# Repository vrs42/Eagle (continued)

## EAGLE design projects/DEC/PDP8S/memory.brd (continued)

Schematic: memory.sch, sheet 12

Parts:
A03: R001S; H807S
A04: R202S; H807S
A09: R107S; H807S
A11, A34: R111S; H807S
A12: R002S; H807S
A16: R602U; H807S
A19: R603S; H807S
B02: W023S; H807S
B03: W050S; H807S
B04: R202S; H807S
B05: W005S; H807S
B18: R603S; H807S
B24: R113S; H807S
B33: R107S; H807S
B39: W028S; H807S
C02: W023S; H807S
C04: R202S; H807S
C05: R107S; H807S
D02: W023S; H807S
D03: W050S; H807S
D04: R202S; H807S
D05: R107S; H807S
D06: R113S; H807S
E02: W023S; H807S
E03: R001S; H807S
E04: R202S; H807S
E08: W005S; H807S
E37, E38, E39: W028S; H807S
F03, F04: R202S; H807S
F06: R001S; H807S
F08, F09: R111S; H807S
F10: R107S; H807S
F14: R113S; H807S

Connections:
-15V: A03.B2 (-15V), A04.B2 (-15V), A09.B2 (-15V), A11.B2 (-15V), A12.B2 (-15V), A16.B2 (-15V), A19.B2 (-15V), A34.B2 (-15V), B03.B2 (-15V), B04.B2 (-15V), B05.B2 (-15V), B18.B2 (-15V), B24.B2 (-15V), B33.B2 (-15V), C04.B2 (-15V), C05.B2 (-15V), D03.B2 (-15V), D04.B2 (-15V), D05.B2 (-15V), D06.B2 (-15V), E03.B2 (-15V), E04.B2 (-15V), E08.B2 (-15V), F03.B2 (-15V), F04.B2 (-15V), F06.B2 (-15V), F08.B2 (-15V), F09.B2 (-15V), F10.B2 (-15V), F14.B2 (-15V); also elsewhere on the board
-(DP+EP): A19.P2; also elsewhere on the board
-(SP+PCP): A19.J2; also elsewhere on the board
-(WTX*ROTR): A16.F2 (F); also elsewhere on the board
-(WTX*TAD): A16.J2 (J); also elsewhere on the board
-A12: A16.H2 (H), A19.D2 (PU0); also elsewhere on the board
-A(00-01): A16.E2 (E); also elsewhere on the board
-A(00-11): B18.K2 (PU0); also elsewhere on the board
-AC11: A03.E2 (E), A04.T2 (1), A09.S2; also elsewhere on the board
-BAC00: D05.F2, E39.D2
-BAC01: D05.J2, E39.E2
-BAC02: D05.L2, E39.H2
-BAC03: D05.N2, E39.K2
-BAC04: D05.R2, E39.M2
-BAC05: D05.T2, E39.P2
-BAC06: C05.F2, E39.S2
-BAC07: C05.J2, E39.T2
-BAC08: C05.L2, E39.V2
-BAC09: B39.D2, C05.N2
-BAC10: B39.E2, C05.R2
-BAC11: B39.H2, C05.D2
-CAC: A04.M2 (SET), A19.F2 (O), A19.M2 (O), B04.M2 (SET), C04.M2 (SET), D04.M2 (SET), E04.M2 (SET), F04.M2 (SET); also elsewhere on the board
-CL: F03.F2 (RESET); also elsewhere on the board
-IC00: B05.V2, E03.D2 (D), E38.D2
-IC01: B05.U2, E03.F2 (D), E38.E2
-IC02: B05.T2, E03.J2 (D), E38.H2
-IC03: B05.S2, E03.L2 (D), E38.K2
-IC04: B05.R2, E03.N2 (D), E38.M2
-IC05: A03.T2 (D), B05.P2, E38.P2
-IC06: A03.R2 (D), B05.N2, E38.S2
-IC07: A03.N2 (D), B05.M2, E38.T2
-IC08: A03.L2 (D), B05.L2, E38.V2
-IC09: A03.J2 (D), B05.K2, E37.D2
-IC10: A03.F2 (D), B05.J2, E37.E2
-IC11: A03.D2 (D), B05.H2, E37.H2
-L: F03.H2 (0), F06.E2 (E); also elsewhere on the board
-LP: A19.K2 (PU0); also elsewhere on the board
-LSH: F03.D2 (PU0), F03.K2 (PU1); also elsewhere on the board
-SAC00: E08.U2, F04.F2 (RESET); also elsewhere on the board
-SAC01: E08.T2, F04.R2 (RESET); also elsewhere on the board
-SAC02: E04.F2 (RESET), E08.S2; also elsewhere on the board
-SAC03: E04.R2 (RESET), E08.R2; also elsewhere on the board
-SAC04: D04.F2 (RESET), E08.P2; also elsewhere on the board
-SAC05: D04.R2 (RESET), E08.N2; also elsewhere on the board
-SAC06: C04.F2 (RESET), E08.M2; also elsewhere on the board
-SAC07: C04.R2 (RESET), E08.H2; also elsewhere on the board
-SAC08: B04.F2 (RESET), E08.K2; also elsewhere on the board
-SAC09: B04.R2 (RESET), E08.F2; also elsewhere on the board
-SAC10: A04.F2 (RESET), E08.E2; also elsewhere on the board
-SAC11: A04.R2 (RESET), E08.D2; also elsewhere on the board
-SL: F06.D2 (D); also elsewhere on the board
-TAD: F06.J2 (D); also elsewhere on the board
AC00: D03.P2, D05.H2, F04.H2 (0), F04.V2 (EN1); also elsewhere on the board
AC11B: A09.R2, A34.S2, B03.E2, F08.D2, F09.K2; also elsewhere on the board
AND: F06.T2 (D); also elsewhere on the board
AND+TAD+DCA+IAC+CMA+ROTL+OP2: B24.M2; also elsewhere on the board
DC: A34.R2; also elsewhere on the board
EX+DC: B33.H2; also elsewhere on the board
GND: A03.C2 (GND), A04.C2 (GND), A09.C2 (GND), A11.C2 (GND), A12.C2 (GND), A16.C2 (GND), A19.C2 (GND), A19.H2 (G), A19.L2 (EN0), A19.N2 (G), A34.C2 (GND), B03.C2 (GND), B04.C2 (GND), B05.C2 (GND), B18.C2 (GND), B18.N2 (G), B24.C2 (GND), B33.C2 (GND), B39.C2 (GND), B39.F2 (GND), B39.J2 (GND), B39.L2 (GND), B39.N2 (GND), B39.R2 (GND), B39.U2 (GND), C04.C2 (GND), C05.C2 (GND), D03.C2 (GND), D04.C2 (GND), D05.C2 (GND), D06.C2 (GND), E03.C2 (GND), E04.C2 (GND), E08.C2 (GND), E37.C2 (GND), E37.F2 (GND), E37.J2 (GND), E37.L2 (GND), E37.N2 (GND), E37.R2 (GND), E37.U2 (GND), E38.C2 (GND), E38.F2 (GND), E38.J2 (GND), E38.L2 (GND), E38.N2 (GND), E38.R2 (GND), E38.U2 (GND), E39.C2 (GND), E39.F2 (GND), E39.J2 (GND), E39.L2 (GND), E39.N2 (GND), E39.R2 (GND), E39.U2 (GND), F03.C2 (GND), F04.C2 (GND), F06.C2 (GND), F08.C2 (GND), F09.C2 (GND), F10.C2 (GND), F14.C2 (GND); also elsewhere on the board
IAC+CMA: F14.U2; also elsewhere on the board
L: D03.S2, F03.J2 (1), F14.P2; also elsewhere on the board
LD: B33.K2; also elsewhere on the board
MB04: A11.S2, D06.R2; also elsewhere on the board
MB11: F09.L2; also elsewhere on the board
unnamed: D03.M2, D05.K2, E04.L2 (EN1), F04.S2 (0)
unnamed: B03.U2, C04.L2 (EN1), D04.S2 (0), D05.U2
unnamed: B02.R2, B03.F2
unnamed: D03.K2, D05.M2, E04.H2 (0), E04.V2 (EN1)
unnamed: D03.E2, D04.H2 (0), D04.V2 (EN1), D05.S2
unnamed: D03.H2, D04.L2 (EN1), D05.P2, E04.S2 (0)
unnamed: B03.S2, C04.H2 (0), C04.V2 (EN1), C05.H2
unnamed: B03.P2, B04.L2 (EN1), C04.S2 (0), C05.K2
unnamed: A04.L2 (EN1), B03.K2, B04.S2 (0), C05.P2
unnamed: A04.H2 (0), A04.V2 (EN1), B03.H2, C05.S2
unnamed: B02.V2, B03.J2
unnamed: A04.S2 (0), C05.E2
unnamed: B03.L2, C02.H2
unnamed: B03.N2, C02.M2
unnamed: B03.R2, C02.S2
unnamed: B03.T2, D02.E2
unnamed: B03.V2, D02.F2
unnamed: D02.L2, D03.F2
unnamed: D02.R2, D03.J2
unnamed: D03.L2, E02.D2
unnamed: D03.N2, E02.H2
unnamed: D03.R2, E02.M2
unnamed: E03.E2 (E), F04.J2 (1), F04.P2 (EN0)
unnamed: E03.H2 (E), E04.E2 (EN0), F04.T2 (1)
unnamed: E03.K2 (E), E04.J2 (1), E04.P2 (EN0)
unnamed: D04.E2 (EN0), E03.M2 (E), E04.T2 (1)
unnamed: A03.U2 (E), C04.E2 (EN0), D04.T2 (1)
unnamed: D04.J2 (1), D04.P2 (EN0), E03.P2 (E)
unnamed: A03.S2 (E), C04.J2 (1), C04.P2 (EN0)
unnamed: A03.P2 (E), B04.E2 (EN0), C04.T2 (1)
unnamed: A03.M2 (E), B04.J2 (1), B04.P2 (EN0)
unnamed: A03.K2 (E), A04.E2 (EN0), B04.T2 (1)
unnamed: A03.H2 (E), A04.J2 (1), A04.P2 (EN0)
unnamed: A04.D2 (PU0), A04.K2 (PU1), A04.N2 (PU0), A04.U2 (PU1), A16.K2 (K), B04.D2 (PU0), B04.K2 (PU1), B04.N2 (PU0), B04.U2 (PU1), B18.M2 (O), C04.D2 (PU0), C04.K2 (PU1), C04.N2 (PU0), C04.U2 (PU1), D04.D2 (PU0), D04.K2 (PU1), D04.N2 (PU0), D04.U2 (PU1), E04.D2 (PU0), E04.K2 (PU1), E04.N2 (PU0), E04.U2 (PU1), E08.J2, E08.V2, F04.D2 (PU0), F04.K2 (PU1), F04.N2 (PU0), F04.U2 (PU1), F09.V2
unnamed: B03.M2, B04.H2 (0), B04.V2 (EN1), C05.M2
unnamed: A34.U2, D05.E2, F04.E2 (EN0), F09.N2, F09.P2, F09.U2, F14.S2, F14.V2
unnamed: D05.D2, F04.L2 (EN1)
unnamed: F06.U2 (E), F09.M2
unnamed: A11.T2, A12.S2 (F)
unnamed: A11.U2, A19.E2 (EN0), D06.S2
unnamed: D03.T2, E02.S2
unnamed: F03.E2 (EN0), F10.D2
unnamed: B24.S2, F03.L2 (EN1), F08.H2, F08.J2, F10.E2
unnamed: F06.K2 (E), F08.F2
unnamed: B18.L2 (EN0), B24.N2, B33.F2, B33.J2
OP1: A12.P2 (D); also elsewhere on the board
OP2: F09.S2; also elsewhere on the board
ROTR+ROTL+TAD: F08.E2, F14.R2; also elsewhere on the board
S: B24.P2, F09.R2, F14.T2; also elsewhere on the board
TAD+IAC+CMA: B24.R2; also elsewhere on the board
VCC: A03.A2 (VCC), A04.A2 (VCC), A09.A2 (VCC), A11.A2 (VCC), A12.A2 (VCC), A16.A2 (VCC), A19.A2 (VCC), A34.A2 (VCC), B03.A2 (VCC), B04.A2 (VCC), B05.A2 (VCC), B18.A2 (VCC), B24.A2 (VCC), B33.A2 (VCC), C04.A2 (VCC), C05.A2 (VCC), D03.A2 (VCC), D04.A2 (VCC), D05.A2 (VCC), D06.A2 (VCC), E03.A2 (VCC), E04.A2 (VCC), E08.A2 (VCC), F03.A2 (VCC), F04.A2 (VCC), F06.A2 (VCC), F08.A2 (VCC), F09.A2 (VCC), F10.A2 (VCC), F14.A2 (VCC); also elsewhere on the board
WTF: A11.R2; also elsewhere on the board
WTX: B24.L2; also elsewhere on the board
WTX*OP2: D06.P2; also elsewhere on the board

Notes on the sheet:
D-BS-8S-0-20
Accumulator

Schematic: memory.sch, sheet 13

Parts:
B16, B33: R107S; H807S
D36: R111S; H807S
D39: R002S; H807S
E22: R401S; H807S
E23, E24, E25: R202S; H807S
E36: R113S; H807S

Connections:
-15V: B16.B2 (-15V), B33.B2 (-15V), D36.B2 (-15V), D39.B2 (-15V), E22.B2 (-15V), E23.B2 (-15V), E24.B2 (-15V), E25.B2 (-15V), E36.B2 (-15V); also elsewhere on the board
-AM: D36.L2, E23.H2 (0), E23.V2 (EN1), E36.P2
-BM: E23.S2 (0), E24.L2 (EN1), E36.T2
-CM: E24.H2 (0), E24.V2 (EN1)
-DM: E24.S2 (0), E25.L2 (EN1)
-EM: D36.E2, E25.H2 (0), E25.V2 (EN1)
-FM: D39.M2 (E), E23.E2 (EN0), E25.S2 (0), E36.M2
-INHIBIT: B16.S2, B33.U2, E36.S2
-MPC: E23.F2 (RESET), E23.R2 (RESET), E24.F2 (RESET), E24.R2 (RESET), E25.F2 (RESET), E25.R2 (RESET); also elsewhere on the board
-READ: E36.N2; also elsewhere on the board
-STROBE: D36.H2, D36.J2; also elsewhere on the board
-TSH: E22.D2 (D), E23.D2 (PU0), E23.K2 (PU1), E23.N2 (PU0), E23.U2 (PU1), E24.D2 (PU0), E24.K2 (PU1), E24.N2 (PU0), E24.U2 (PU1), E25.D2 (PU0), E25.K2 (PU1), E25.N2 (PU0), E25.U2 (PU1)
-WRITE: E36.V2
-WTMEM_C/W: D39.L2 (D), E36.D2; also elsewhere on the board
-WTMEM_R/W: D36.K2, E36.J2; also elsewhere on the board
AM: E23.J2 (1), E23.P2 (EN0)
BM: E23.T2 (1), E24.E2 (EN0), E36.L2
CM: E24.J2 (1), E24.P2 (EN0)
DM: D36.D2, E24.T2 (1), E25.E2 (EN0), E36.R2
EM: E25.J2 (1), E25.P2 (EN0), E36.U2
FM: E23.L2 (EN1), E25.T2 (1)
GND: B16.C2 (GND), B33.C2 (GND), D36.C2 (GND), D39.C2 (GND), E22.C2 (GND), E23.C2 (GND), E24.C2 (GND), E25.C2 (GND), E36.C2 (GND); also elsewhere on the board
INH1: B33.T2; also elsewhere on the board
INH2: B16.R2
MEMGO: D36.N2, D36.P2, E22.S2 (S); also elsewhere on the board
unnamed: E22.T2 (T), E22.U2 (U)
unnamed: D36.F2, D39.S2 (F)
unnamed: D36.M2, D39.N2 (F)
unnamed: E36.F2, E36.H2
STROBE_EN: D39.R2 (E), E36.E2, E36.K2
VCC: B16.A2 (VCC), B33.A2 (VCC), D36.A2 (VCC), D39.A2 (VCC), E22.A2 (VCC), E23.A2 (VCC), E24.A2 (VCC), E25.A2 (VCC), E36.A2 (VCC); also elsewhere on the board

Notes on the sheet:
D-BS-8S-0-22
Memory Control

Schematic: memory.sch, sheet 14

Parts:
B34: R202S; H807S
C29, C30, C31, C32: R202S; H807S
D29: R107S; H807S
D30: R401S; H807S
D31: R603S; H807S
D32: R113S; H807S
D39: R002S; H807S
E29: R111S; H807S
E37: W028S; H807S
F32: W021S; H807S

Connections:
-15V: B34.B2 (-15V), C29.B2 (-15V), C30.B2 (-15V), C31.B2 (-15V), C32.B2 (-15V), D29.B2 (-15V), D30.B2 (-15V), D31.B2 (-15V), D32.B2 (-15V), D39.B2 (-15V), E29.B2 (-15V); also elsewhere on the board
-(SP+PCP): B34.F2 (RESET); also elsewhere on the board
-A00: B34.D2 (PU0); also elsewhere on the board
-FR: B34.H2 (0); also elsewhere on the board
-IOP2: B34.K2 (PU1); also elsewhere on the board
-LCIF: B34.L2 (EN1), E37.V2
-MCA: C29.H2 (0), C29.P2 (EN0), D39.T2 (D)
-MCB: C29.S2 (0), C30.E2 (EN0)
-MCC: C30.H2 (0), C30.P2 (EN0)
-MCD: C30.S2 (0), C31.E2 (EN0)
-MCE: C31.H2 (0), C31.P2 (EN0)
-MCF: C31.S2 (0), C32.E2 (EN0), D32.E2
-MCG: C32.H2 (0), C32.P2 (EN0)
-MCH: C29.E2 (EN0), C32.S2 (0), D39.U2 (E)
-MPC: C29.F2 (RESET), C29.R2 (RESET), C30.F2 (RESET), C30.R2 (RESET), C31.F2 (RESET), C31.R2 (RESET), C32.F2 (RESET), C32.R2 (RESET), F32.M2; also elsewhere on the board
-[WTX*(JMP+JMS)]: B34.E2 (EN0); also elsewhere on the board
DONE: F32.V2
GND: B34.C2 (GND), C29.C2 (GND), C30.C2 (GND), C31.C2 (GND), C32.C2 (GND), D29.C2 (GND), D30.C2 (GND), D31.C2 (GND), D31.L2 (EN0), D31.N2 (G), D32.C2 (GND), D39.C2 (GND), E29.C2 (GND), E37.C2 (GND), E37.F2 (GND), E37.J2 (GND), E37.L2 (GND), E37.N2 (GND), E37.R2 (GND), E37.U2 (GND), F32.C2 (GND), F32.F2 (GND), F32.J2 (GND), F32.L2 (GND), F32.N2 (GND), F32.R2 (GND), F32.U2 (GND); also elsewhere on the board
INHIBIT: D29.J2, F32.H2
MCA: C29.J2 (1), C29.V2 (EN1), D32.D2
MCB: C29.T2 (1), C30.L2 (EN1), D32.L2
MCC: C30.J2 (1), C30.V2 (EN1), D32.H2
MCD: C30.T2 (1), C31.L2 (EN1)
MCE: C31.J2 (1), C31.V2 (EN1)
MCF: C31.T2 (1), C32.L2 (EN1)
MCG: C32.J2 (1), C32.V2 (EN1), D32.M2
MCH: C29.L2 (EN1), C32.T2 (1), D32.J2
MEM_DONE: D31.M2 (O), F32.P2
unnamed: D39.V2 (F), E29.F2
unnamed: D30.T2 (T), D30.U2 (U)
unnamed: D30.S2 (S), D31.K2 (PU0), E29.H2
unnamed: C29.D2 (PU0), C29.K2 (PU1), C29.N2 (PU0), C29.U2 (PU1), C30.D2 (PU0), C30.K2 (PU1), C30.N2 (PU0), C30.U2 (PU1), C31.D2 (PU0), C31.K2 (PU1), C31.N2 (PU0), C31.U2 (PU1), C32.D2 (PU0), C32.K2 (PU1), C32.N2 (PU0), C32.U2 (PU1), D30.D2 (D)
unnamed: D29.M2, D32.P2, D32.V2
unnamed: D32.S2, D32.T2
unnamed: D29.E2, D32.F2
unnamed: D29.H2, D32.K2
unnamed: D29.K2, D32.N2
RD_RQ: D32.U2, E29.D2, F32.S2
READ: D29.D2, F32.D2; also elsewhere on the board
STROBE_ENABLE: D29.L2, F32.K2
VCC: B34.A2 (VCC), C29.A2 (VCC), C30.A2 (VCC), C31.A2 (VCC), C32.A2 (VCC), D29.A2 (VCC), D30.A2 (VCC), D31.A2 (VCC), D32.A2 (VCC), D39.A2 (VCC), E29.A2 (VCC); also elsewhere on the board
WRITE: D29.F2, F32.E2; also elsewhere on the board
WR_RQ: D32.R2, E29.E2, F32.T2

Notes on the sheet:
D-BS-OMD8S-0-4 (1)
OMD8S Connectors and Logic (in 8S)

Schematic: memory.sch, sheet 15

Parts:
A19: R603S; H807S
A21: R111S; H807S
A37: R602S; H807S
B19, B22: R603S; H807S
D29: R107S; H807S
D31: R603S; H807S
E29: R111S; H807S
E30, E31, E32: W021S; H807S
F02: W023S; H807S
F24, F25: R107S; H807S
F29, F30, F31: W021S; H807S
F36: R113S; H807S

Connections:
(ISZ+DCA)(B): E30.S2
-15V: A19.B2 (-15V), A21.B2 (-15V), A37.B2 (-15V), B19.B2 (-15V), B22.B2 (-15V), D29.B2 (-15V), D31.B2 (-15V), E29.B2 (-15V), F24.B2 (-15V), F25.B2 (-15V), F36.B2 (-15V); also elsewhere on the board
-(JMP+JMS)(B): E29.N2, F31.P2
-(SP+PCP): A19.V2; also elsewhere on the board
-A: B19.D2 (PU0); also elsewhere on the board
-A00: A37.P2 (E), D31.R2 (PU0); also elsewhere on the board
-A12: B22.J2; also elsewhere on the board
-A13: A19.R2 (PU0), D31.J2; also elsewhere on the board
-A13(B): D31.F2 (O), E32.V2
-BT00(B): E30.T2, F25.T2
-CLK: A37.S2 (H); also elsewhere on the board
-CLR: A37.U2 (K), E31.H2
-JMP: E29.K2; also elsewhere on the board
-JMS: E29.L2; also elsewhere on the board
-LD: D29.P2; also elsewhere on the board
-LP: A37.V2 (L); also elsewhere on the board
-MA00: F24.E2; also elsewhere on the board
-MA01: F24.H2; also elsewhere on the board
-MA02: F24.K2; also elsewhere on the board
-MA03: F24.M2; also elsewhere on the board
-MA04: F24.P2; also elsewhere on the board
-MA05: F24.S2; also elsewhere on the board
-MA06: F24.U2; also elsewhere on the board
-MA07: F25.E2; also elsewhere on the board
-MA08: F25.H2; also elsewhere on the board
-MA09: F25.K2; also elsewhere on the board
-MA10: F25.M2; also elsewhere on the board
-MA11: F25.P2; also elsewhere on the board
-MEM00: F30.K2; also elsewhere on the board
-MEM01: F30.M2; also elsewhere on the board
-MEM02: F30.P2; also elsewhere on the board
-MEM03: F30.S2; also elsewhere on the board
-MEM04: F30.T2; also elsewhere on the board
-MEM05: F30.V2; also elsewhere on the board
-MEM06: E32.D2; also elsewhere on the board
-MEM07: E32.E2; also elsewhere on the board
-MEM08: E32.H2; also elsewhere on the board
-MEM09: E32.K2; also elsewhere on the board
-MEM10: E32.M2; also elsewhere on the board
-MEM11: E32.P2; also elsewhere on the board
-PPC: A37.T2 (J); also elsewhere on the board
-RSF: A19.T2 (O), F31.H2
-T3: F36.E2; also elsewhere on the board
-WTB: A37.R2 (F), D31.S2 (EN0); also elsewhere on the board
-WTD: D29.S2; also elsewhere on the board
-WTF: D29.U2; also elsewhere on the board
A11(B): B19.F2 (O), F31.K2
A12(B): A21.J2, B22.F2 (O), F31.M2
BMA0: F24.D2, F29.D2
BMA1: F24.F2, F29.E2
BMA2: F24.J2, F29.H2
BMA3: F24.L2, F29.K2
BMA4: F24.N2, F29.M2
BMA5: F24.R2, F29.P2
BMA6: F24.T2, F29.S2
BMA7: F25.D2, F29.T2
BMA8: F25.F2, F29.V2
BMA9: F25.J2, F30.D2
BMA10: F25.L2, F30.E2
BMA11: F25.N2, F30.H2
BT00: F25.U2; also elsewhere on the board
DF0: E31.M2, F02.M2
DF1: E31.P2, F02.L2
DF2: E31.S2, F02.K2
GND: A19.C2 (GND), A19.U2 (G), A21.C2 (GND), A37.N2 (C), B19.C2 (GND), B19.H2 (G), B22.C2 (GND), B22.H2 (G), D29.C2 (GND), D31.C2 (GND), D31.H2 (G), D31.U2 (G), E29.C2 (GND), E30.C2 (GND), E30.F2 (GND), E30.J2 (GND), E30.L2 (GND), E30.N2 (GND), E30.R2 (GND), E30.U2 (GND), E31.C2 (GND), E31.F2 (GND), E31.J2 (GND), E31.L2 (GND), E31.N2 (GND), E31.R2 (GND), E31.U2 (GND), E32.C2 (GND), E32.F2 (GND), E32.J2 (GND), E32.L2 (GND), E32.N2 (GND), E32.R2 (GND), E32.U2 (GND), F24.C2 (GND), F25.C2 (GND), F29.C2 (GND), F29.F2 (GND), F29.J2 (GND), F29.L2 (GND), F29.N2 (GND), F29.R2 (GND), F29.U2 (GND), F30.C2 (GND), F30.F2 (GND), F30.J2 (GND), F30.L2 (GND), F30.N2 (GND), F30.R2 (GND), F30.U2 (GND), F31.C2 (GND), F31.F2 (GND), F31.J2 (GND), F31.L2 (GND), F31.N2 (GND), F31.R2 (GND), F31.U2 (GND), F36.C2 (GND); also elsewhere on the board
IF0: E31.T2, F02.J2
IF1: E31.V2, F02.H2
IF2: E32.T2, F02.F2
IOT: F31.V2; also elsewhere on the board
LD(B): D29.N2, E31.K2
MPS: E32.S2
unnamed: B19.E2 (EN0), F36.F2
READ: F31.E2; also elsewhere on the board
SDF0: E30.D2; also elsewhere on the board
SDF1: E30.E2; also elsewhere on the board
SDF2: E30.H2; also elsewhere on the board
SIF0: E30.K2; also elsewhere on the board
SIF1: E30.M2; also elsewhere on the board
SIF2: E30.P2; also elsewhere on the board
T4: F36.D2; also elsewhere on the board
VCC: A19.A2 (VCC), A21.A2 (VCC), A37.A2 (VCC), B19.A2 (VCC), B22.A2 (VCC), D29.A2 (VCC), D31.A2 (VCC), E29.A2 (VCC), F24.A2 (VCC), F25.A2 (VCC), F36.A2 (VCC); also elsewhere on the board
WRITE: F31.D2; also elsewhere on the board
WTB*A00(B): D31.T2 (O), E31.E2
WTD(B): D29.R2, F31.S2
WTF(B): D29.T2, F31.T2
WTGB1: A19.S2 (EN0)
WTX: F25.S2; also elsewhere on the board
WTX(B): E31.D2, F25.R2
WTX*(JMP+JMS): E29.R2; also elsewhere on the board
WTX*(JMP+JMS)(B): E29.U2, E29.V2, E30.V2

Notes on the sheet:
D-BS-OMD8S-0-4 (2)
OMD8S Connectors and Logic (in 8S)

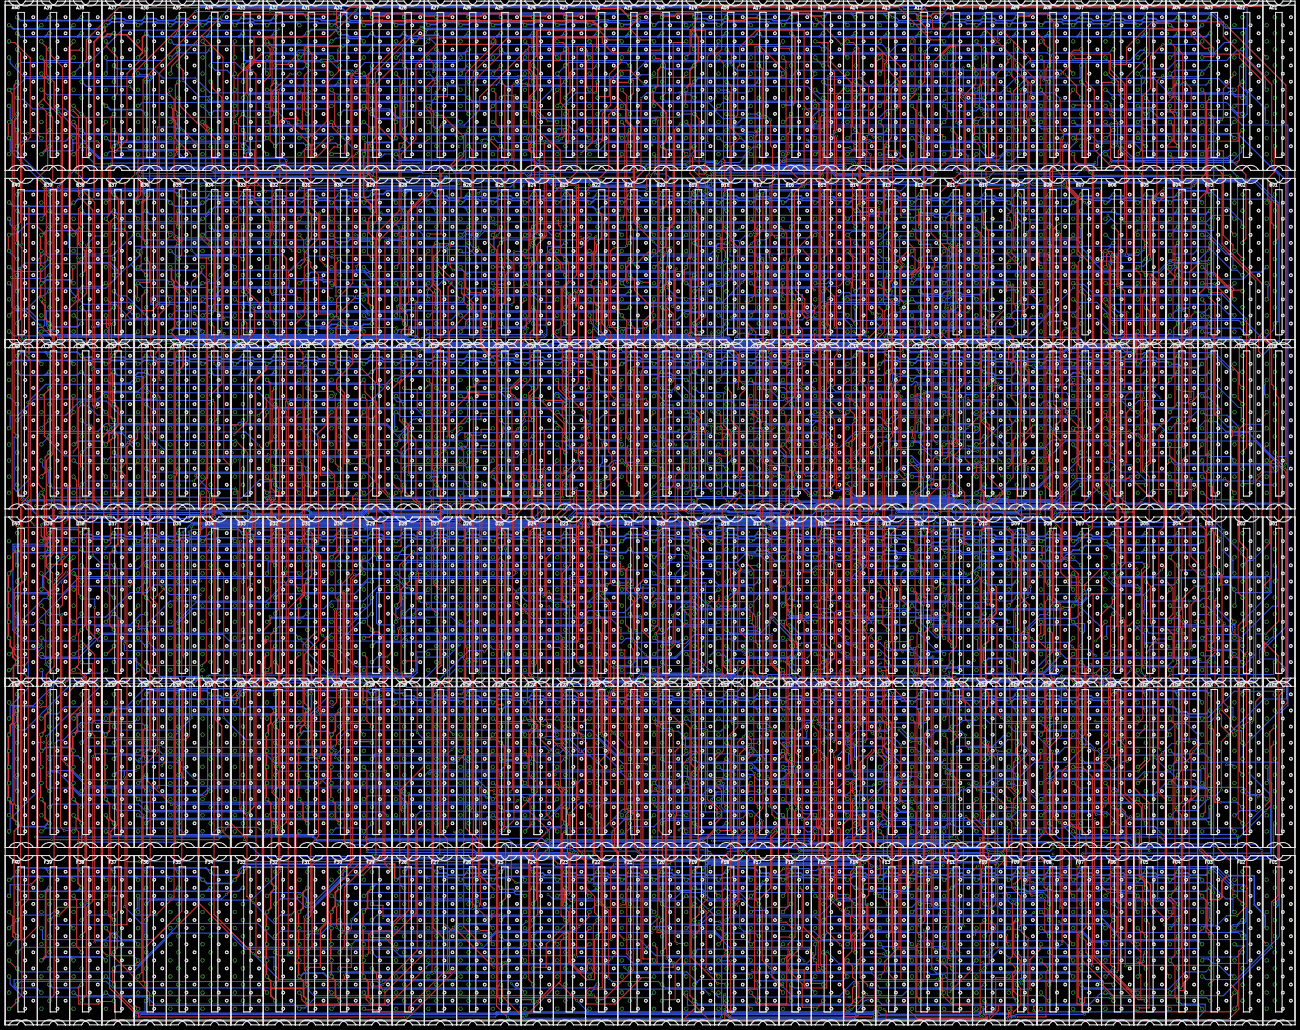
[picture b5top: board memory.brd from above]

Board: 4 copper layers, 508.0 x 401.6 mm, 240 parts (0 on the bottom side), 774 nets.
